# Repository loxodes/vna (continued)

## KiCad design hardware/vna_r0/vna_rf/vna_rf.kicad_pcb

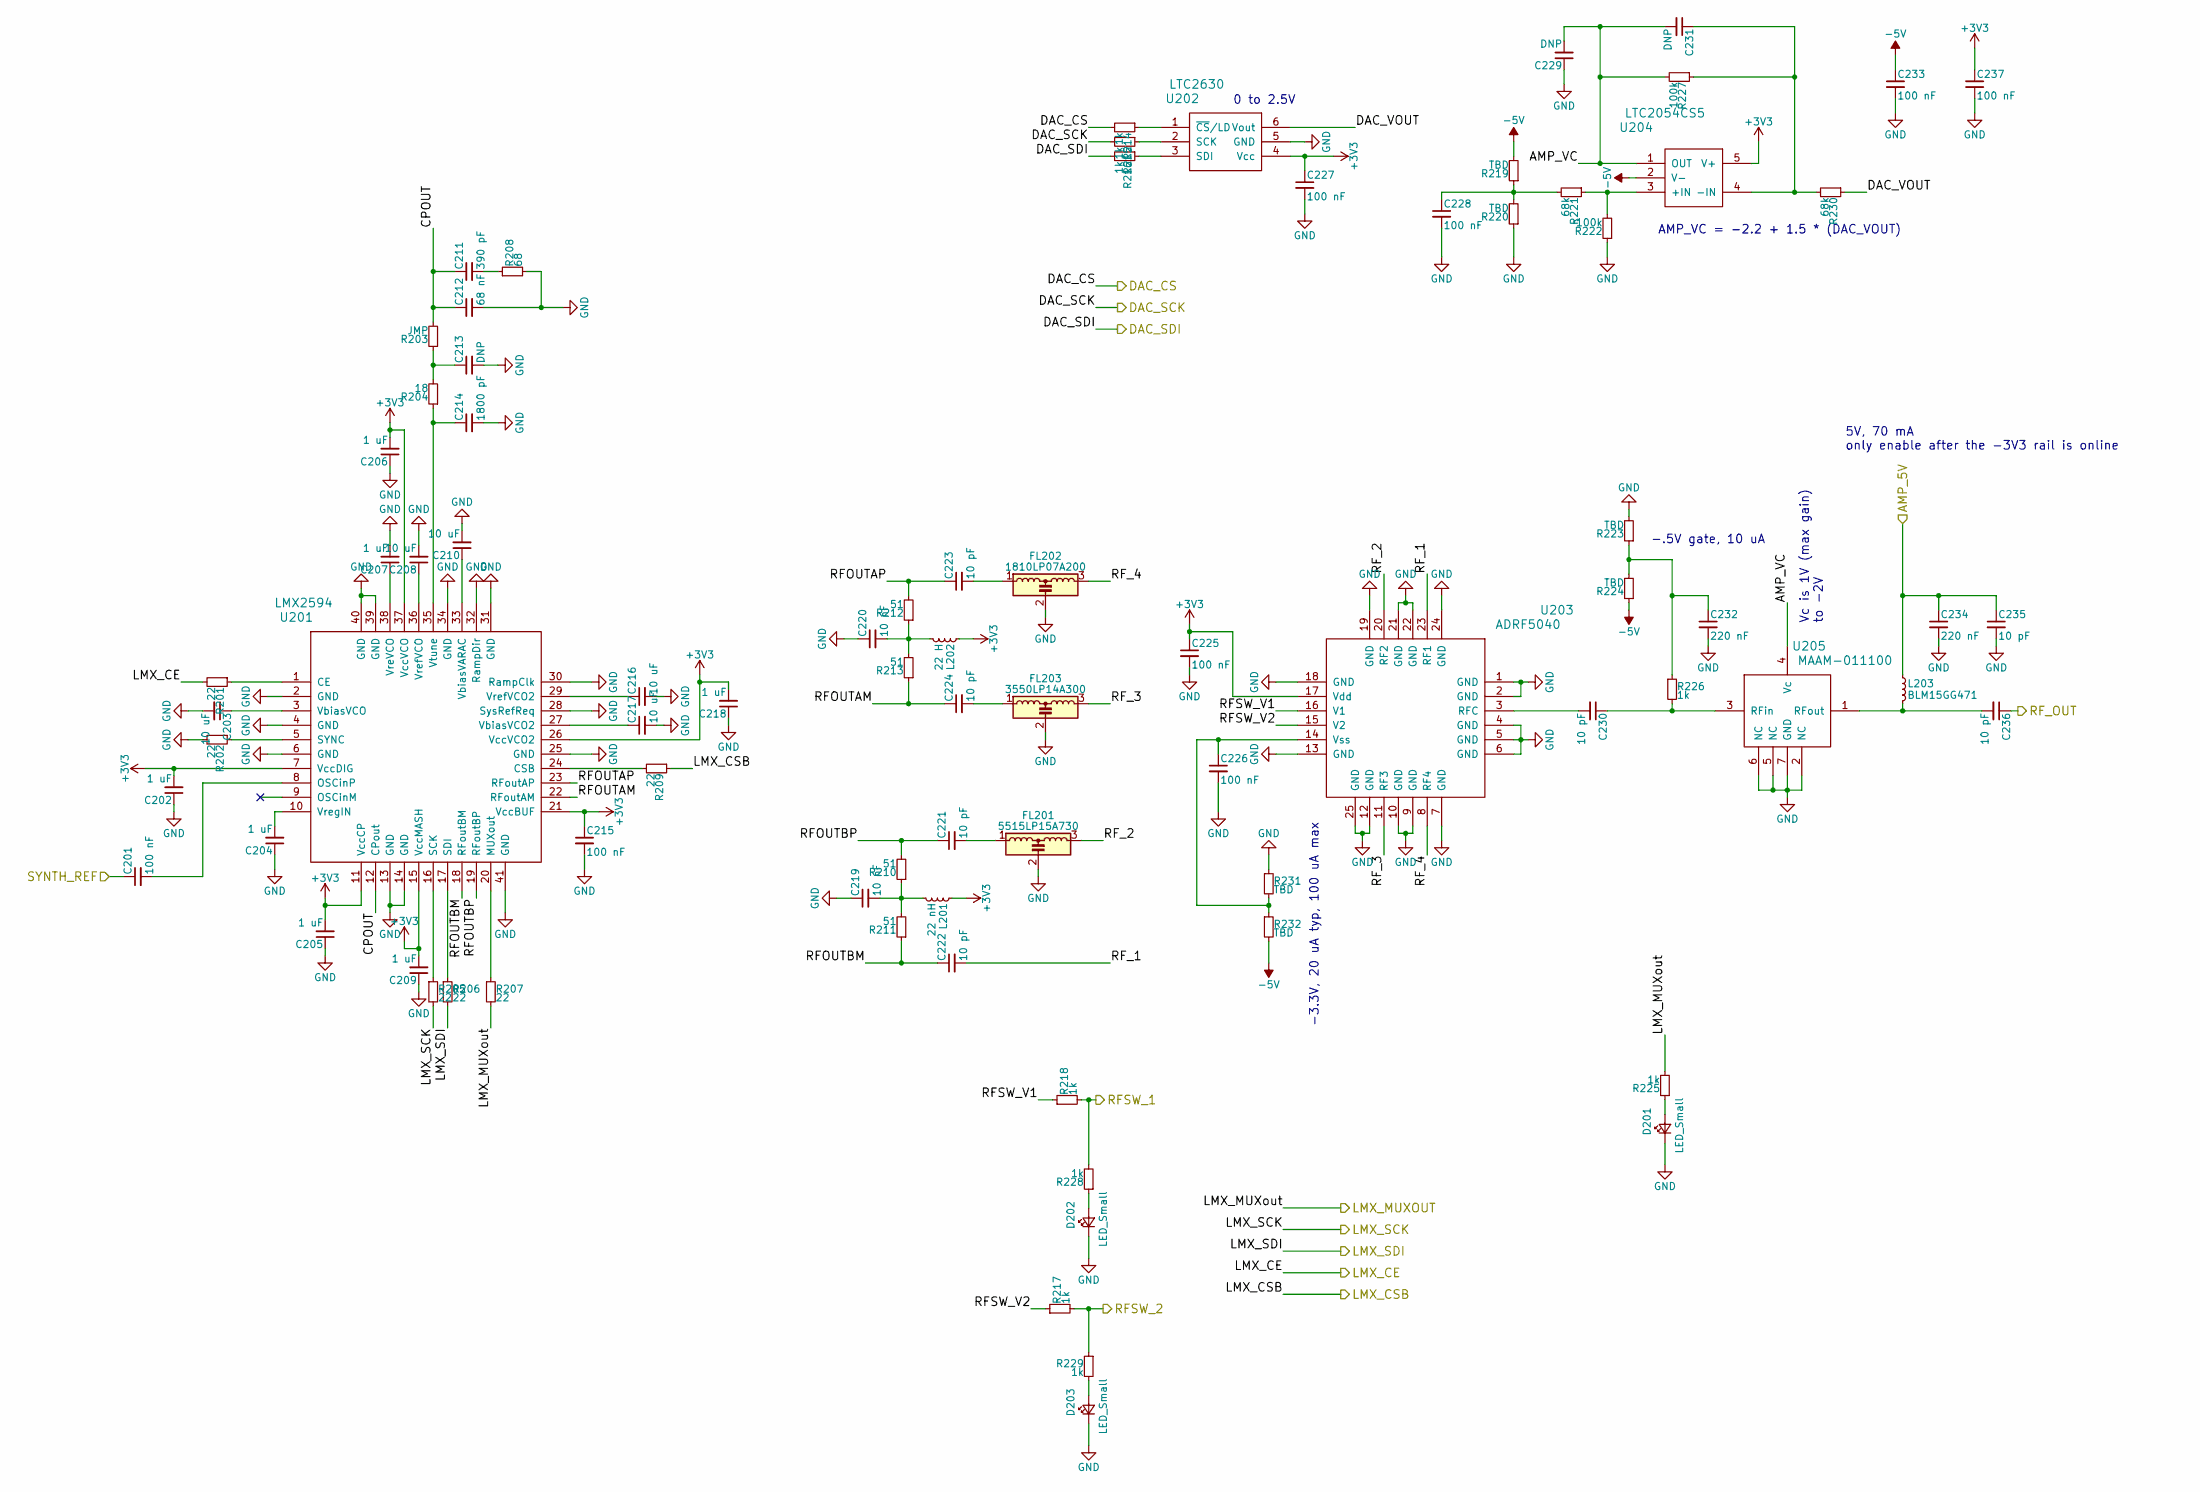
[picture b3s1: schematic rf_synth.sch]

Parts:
C201, C215, C225, C226, C227, C228, C233, C237: 100 nF; C_0402
C202, C204, C205, C206, C207, C209, C218: 1 uF; C_0402
C203, C208, C210, C216, C217: 10 uF; C_0603
C211: 390 pF; C_0402
C212: 68 nF; C_0402
C213, C229, C231: DNP; C_0402
C214: 1800 pF; C_0402
C219, C220: 10 nF; C_0402
C221, C222, C223, C224, C230, C235, C236: 10 pF; C_0402
C232, C234: 220 nF; C_0402
D201, D202, D203: LED_Small; LED_0603
FL201: 5515LP15A730
FL202: 1810LP07A200
FL203: 3550LP14A300
L201: 22 nH; R_0402
L202: 22 H; R_0402
L203: BLM15GG471; R_0402
R201, R202, R205, R206, R207, R209: 22; R_0402
R203: JMP; R_0402
R204: 18; R_0402
R208: 68; R_0402
R210, R211, R212, R213: 51; R_0402
R214, R215, R216, R217, R218, R225, R226, R228, R229: 1k; R_0402
R219, R220, R223, R224, R231, R232: TBD; R_0402
R221, R230: 68k; R_0402
R222, R227: 100k; R_0402
U201: LMX2594; QFN-40-1EP_6x6mm_Pitch0.5mm
U202: LTC2630; SC-70-6
U203: ADRF5040; QFN-24-1EP_4x4mm_Pitch0.5mm
U204: LTC2054CS5; SOT-23-5
U205: MAAM-011100; TDFN6

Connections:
+3V3: C202.2, C205.2, C206.2, C209.2, C215.1, C218.2, C225.1, C227.1, C237.1, L201.1, L202.1, U201.7 (VccDIG), U201.11 (VccCP), U201.15 (VccMASH), U201.21 (VccBUF), U201.26 (VccVCO2), U201.37 (VccVCO), U202.4 (Vcc), U203.17 (Vdd), U204.5 (V+); also elsewhere on the board
-5V: C233.1, R219.2, R224.1, R232.2, U204.2 (V-); also elsewhere on the board
/AMP_5V: C234.1, C235.1, L203.1; also elsewhere on the board
/DAC_CS: R214.2; also elsewhere on the board
/DAC_SCK: R215.2; also elsewhere on the board
/DAC_SDI: R216.2; also elsewhere on the board
/LMX_CE: R201.2; also elsewhere on the board
/LMX_CS: R209.1; also elsewhere on the board
/LMX_MUXOUT: R207.2, R225.2; also elsewhere on the board
/LMX_SCK: R205.2; also elsewhere on the board
/LMX_SDI: R206.2; also elsewhere on the board
/RFSW_1: R218.2, R228.2; also elsewhere on the board
/RFSW_2: R217.2, R229.1; also elsewhere on the board
/conn_power/SYNTH_REF: C201.1; also elsewhere on the board
/port_switch/RFIN: C236.1; also elsewhere on the board
/rf_synth/AMP_VC: C229.2, C231.2, R227.2, U204.1 (OUT), U205.4 (Vc)
/rf_synth/CPOUT: C211.1, C212.1, R203.2, U201.12 (CPout)
/rf_synth/DAC_VOUT: R230.1, U202.6 (Vout)
/rf_synth/RFOUTAM: C224.1, R213.1, U201.22 (RFoutAM)
/rf_synth/RFOUTAP: C223.1, R212.2, U201.23 (RFoutAP)
/rf_synth/RFOUTBM: C222.1, R211.1, U201.18 (RFoutBM)
/rf_synth/RFOUTBP: C221.1, R210.2, U201.19 (RFoutBP)
/rf_synth/RFSW_V1: R218.1, U203.16 (V1)
/rf_synth/RFSW_V2: R217.1, U203.15 (V2)
/rf_synth/RF_1: C222.2, U203.23 (RF1)
/rf_synth/RF_2: FL201.3, U203.20 (RF2)
/rf_synth/RF_3: FL203.3, U203.11 (RF3)
/rf_synth/RF_4: FL202.3, U203.8 (RF4)
GND: C202.1, C203.2, C204.1, C205.1, C206.1, C207.2, C208.2, C209.1, C210.2, C212.2, C213.2, C214.2, C215.2, C216.2, C217.2, C218.1, C219.1, C220.1, C225.2, C226.2, C227.2, C228.2, C229.1, C232.2, C233.2, C234.2, C235.2, C237.2, D201.1 (K), D202.1 (K), D203.1 (K), FL201.2, FL202.2, FL203.2, R202.2, R208.2, R220.1, R222.1, R223.2, R231.1, U201.2 (GND), U201.4 (GND), U201.6 (GND), U201.13 (GND), U201.14 (GND), U201.25 (GND), U201.28 (SysRefReq), U201.30 (RampClk), U201.31 (GND), U201.32 (RampDir), U201.34 (GND), U201.39 (GND), U201.40 (GND), U201.41 (GND), U202.5 (GND), U203.1 (GND), U203.2 (GND), U203.4 (GND), U203.5 (GND), U203.6 (GND), U203.7 (GND), U203.9 (GND), U203.10 (GND), U203.12 (GND), U203.13 (GND), U203.18 (GND), U203.19 (GND), U203.21 (GND), U203.22 (GND), U203.24 (GND), U203.25 (GND), U205.2 (NC), U205.5 (NC), U205.6 (NC), U205.7 (GND); also elsewhere on the board
unnamed: C201.2, U201.8 (OSCinP)
unnamed: C203.1, U201.3 (VbiasVCO)
unnamed: C204.2, U201.10 (VregIN)
unnamed: C207.1, U201.38 (VreVCO)
unnamed: C208.1, U201.36 (VrefVCO)
unnamed: C210.1, U201.33 (VbiasVARAC)
unnamed: C211.2, R208.1
unnamed: C213.1, R203.1, R204.2
unnamed: C214.1, R204.1, U201.35 (Vtune)
unnamed: C216.1, U201.29 (VrefVCO2)
unnamed: C217.1, U201.27 (VbiasVCO2)
unnamed: C219.2, L201.2, R210.1, R211.2
unnamed: C220.2, L202.2, R212.1, R213.2
unnamed: C221.2, FL201.1
unnamed: C223.2, FL202.1
unnamed: C224.2, FL203.1
unnamed: C226.1, R231.2, R232.1, U203.14 (Vss)
unnamed: C228.1, R219.1, R220.2, R221.2
unnamed: C230.1, R226.2, U205.3 (RFin)
unnamed: C230.2, U203.3 (RFC)
unnamed: C231.1, R227.1, R230.2, U204.4 (-IN)
unnamed: C232.1, R223.1, R224.2, R226.1
unnamed: C236.2, L203.2, U205.1 (RFout)
unnamed: D201.2 (A), R225.1
unnamed: D202.2 (A), R228.1
unnamed: D203.2 (A), R229.2
unnamed: R201.1, U201.1 (CE)
unnamed: R202.1, U201.5 (SYNC)
unnamed: R205.1, U201.16 (SCK)
unnamed: R206.1, U201.17 (SDI)
unnamed: R207.1, U201.20 (MUXout)
unnamed: R209.2, U201.24 (CSB)
unnamed: R214.1, U202.1 (~CS~/LD)
unnamed: R215.1, U202.2 (SCK)
unnamed: R216.1, U202.3 (SDI)
unnamed: R221.1, R222.2, U204.3 (+IN)

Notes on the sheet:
-.5V gate, 10 uA
5V, 70 mA only enable after the -3V3 rail is online
Vc is 1V (max gain) to -2V
0 to 2.5V
AMP_VC = -2.2 + 1.5 * (DAC_VOUT)
-3.3V, 20 uA typ, 100 uA max

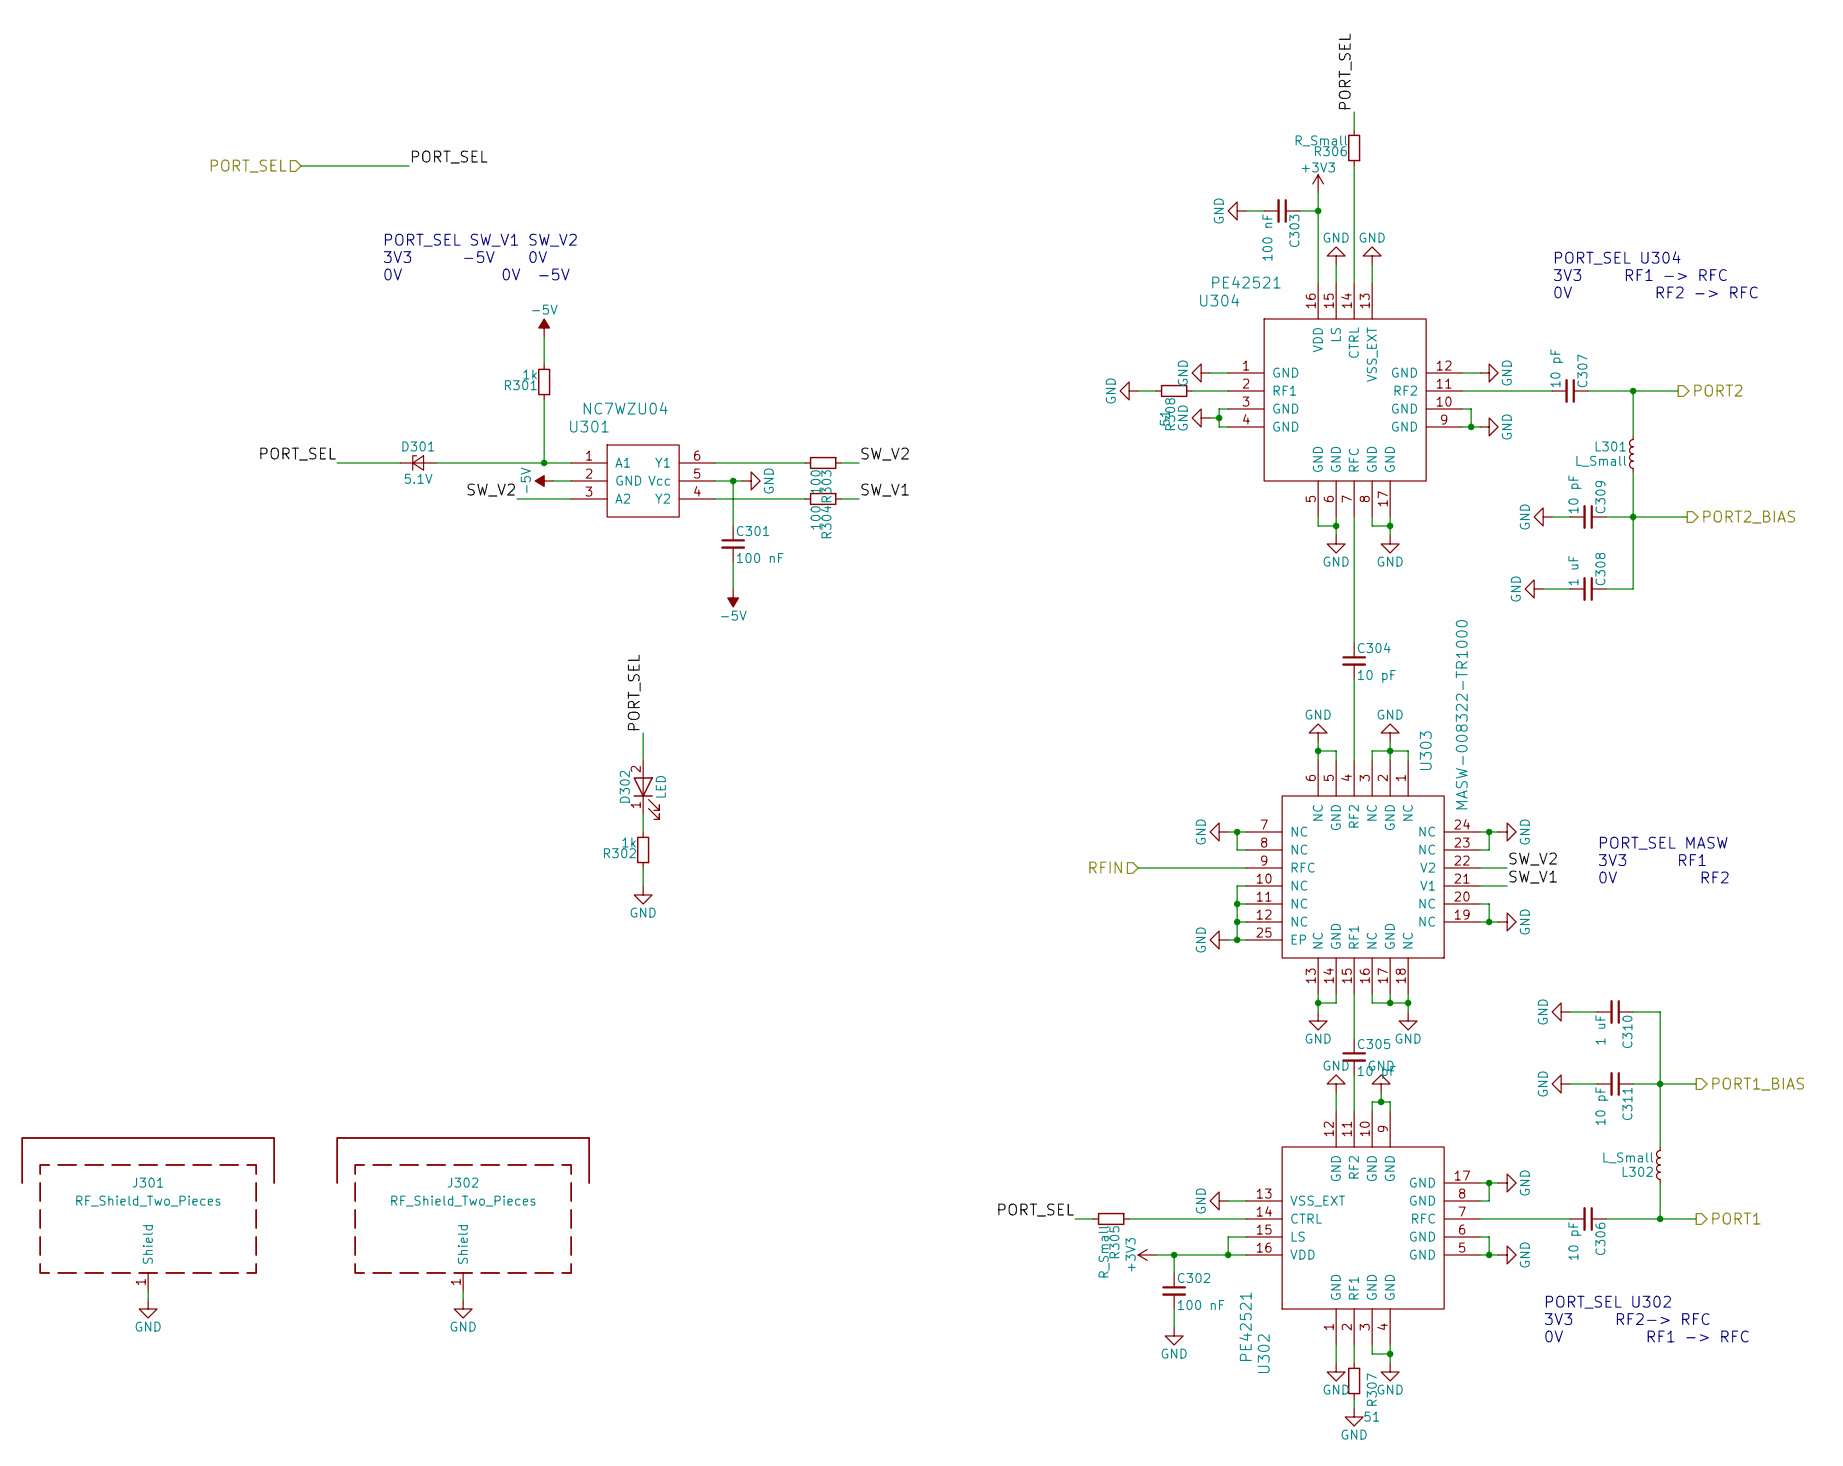
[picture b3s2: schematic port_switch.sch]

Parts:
C301, C302, C303: 100 nF; C_0402
C304, C305, C306, C307, C309, C311: 10 pF; C_0402
C308, C310: 1 uF; C_0805
D301: 5.1V; SOD-323
D302: LED; LED_0603
J301, J302: RF_Shield_Two_Pieces; Laird_Technologies_BMI-S-202-F_16.50x16.50mm
L301, L302: L_Small; ATC506WLS
R301, R302: 1k; R_0402
R303, R304: 100; R_0402
R305, R306: R_Small; R_0402
R307, R308: 51; R_0402
U301: NC7WZU04; SC-70-6
U302, U304: PE42521; QFN-16-1EP_3x3mm_Pitch0.5mm
U303: MASW-008322-TR1000; QFN-24-1EP_4x4mm_Pitch0.5mm

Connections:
+3V3: C302.1, C303.1, U302.15 (LS), U302.16 (VDD), U304.16 (VDD); also elsewhere on the board
-5V: C301.2, R301.2, U301.2 (GND); also elsewhere on the board
/PORT1_BIAS: C310.1, C311.1, L302.2; also elsewhere on the board
/PORT2_BIAS: C308.1, C309.1, L301.2; also elsewhere on the board
/conn_power/PORT1: C306.1, L302.1; also elsewhere on the board
/conn_power/PORT2: C307.1, L301.1; also elsewhere on the board
/conn_power/PORT_SEL: D301.1 (K), D302.2 (A), R305.2, R306.2; also elsewhere on the board
/port_switch/RFIN: U303.9 (RFC); also elsewhere on the board
/port_switch/SW_V1: R304.1, U303.21 (V1)
/port_switch/SW_V2: R303.1, U301.3 (A2), U303.22 (V2)
GND: C301.1, C302.2, C303.2, C308.2, C309.2, C310.2, C311.2, J301.1, J302.1, R302.1, R307.1, R308.1, U301.5 (Vcc), U302.1 (GND), U302.3 (GND), U302.4 (GND), U302.5 (GND), U302.6 (GND), U302.8 (GND), U302.9 (GND), U302.10 (GND), U302.12 (GND), U302.13 (VSS_EXT), U302.17 (GND), U303.1 (NC), U303.2 (GND), U303.3 (NC), U303.5 (GND), U303.6 (NC), U303.7 (NC), U303.8 (NC), U303.10 (NC), U303.11 (NC), U303.12 (NC), U303.13 (NC), U303.14 (GND), U303.16 (NC), U303.17 (GND), U303.18 (NC), U303.19 (NC), U303.20 (NC), U303.23 (NC), U303.24 (NC), U303.25 (EP), U304.1 (GND), U304.3 (GND), U304.4 (GND), U304.5 (GND), U304.6 (GND), U304.8 (GND), U304.9 (GND), U304.10 (GND), U304.12 (GND), U304.13 (VSS_EXT), U304.15 (LS), U304.17 (GND); also elsewhere on the board
unnamed: C304.1, U304.7 (RFC)
unnamed: C304.2, U303.4 (RF2)
unnamed: C305.1, U303.15 (RF1)
unnamed: C305.2, U302.11 (RF2)
unnamed: C306.2, U302.7 (RFC)
unnamed: C307.2, U304.11 (RF2)
unnamed: D301.2 (A), R301.1, U301.1 (A1)
unnamed: D302.1 (K), R302.2
unnamed: R303.2, U301.6 (Y1)
unnamed: R304.2, U301.4 (Y2)
unnamed: R305.1, U302.14 (CTRL)
unnamed: R306.1, U304.14 (CTRL)
unnamed: R307.2, U302.2 (RF1)
unnamed: R308.2, U304.2 (RF1)

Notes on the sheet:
PORT_SEL SW_V1 SW_V2 3V3 -5V 0V 0V 0V -5V
PORT_SEL MASW 3V3 RF1 0V RF2
PORT_SEL U304 3V3 RF1 -> RFC 0V RF2 -> RFC
PORT_SEL U302 3V3 RF2-> RFC 0V RF1 -> RFC

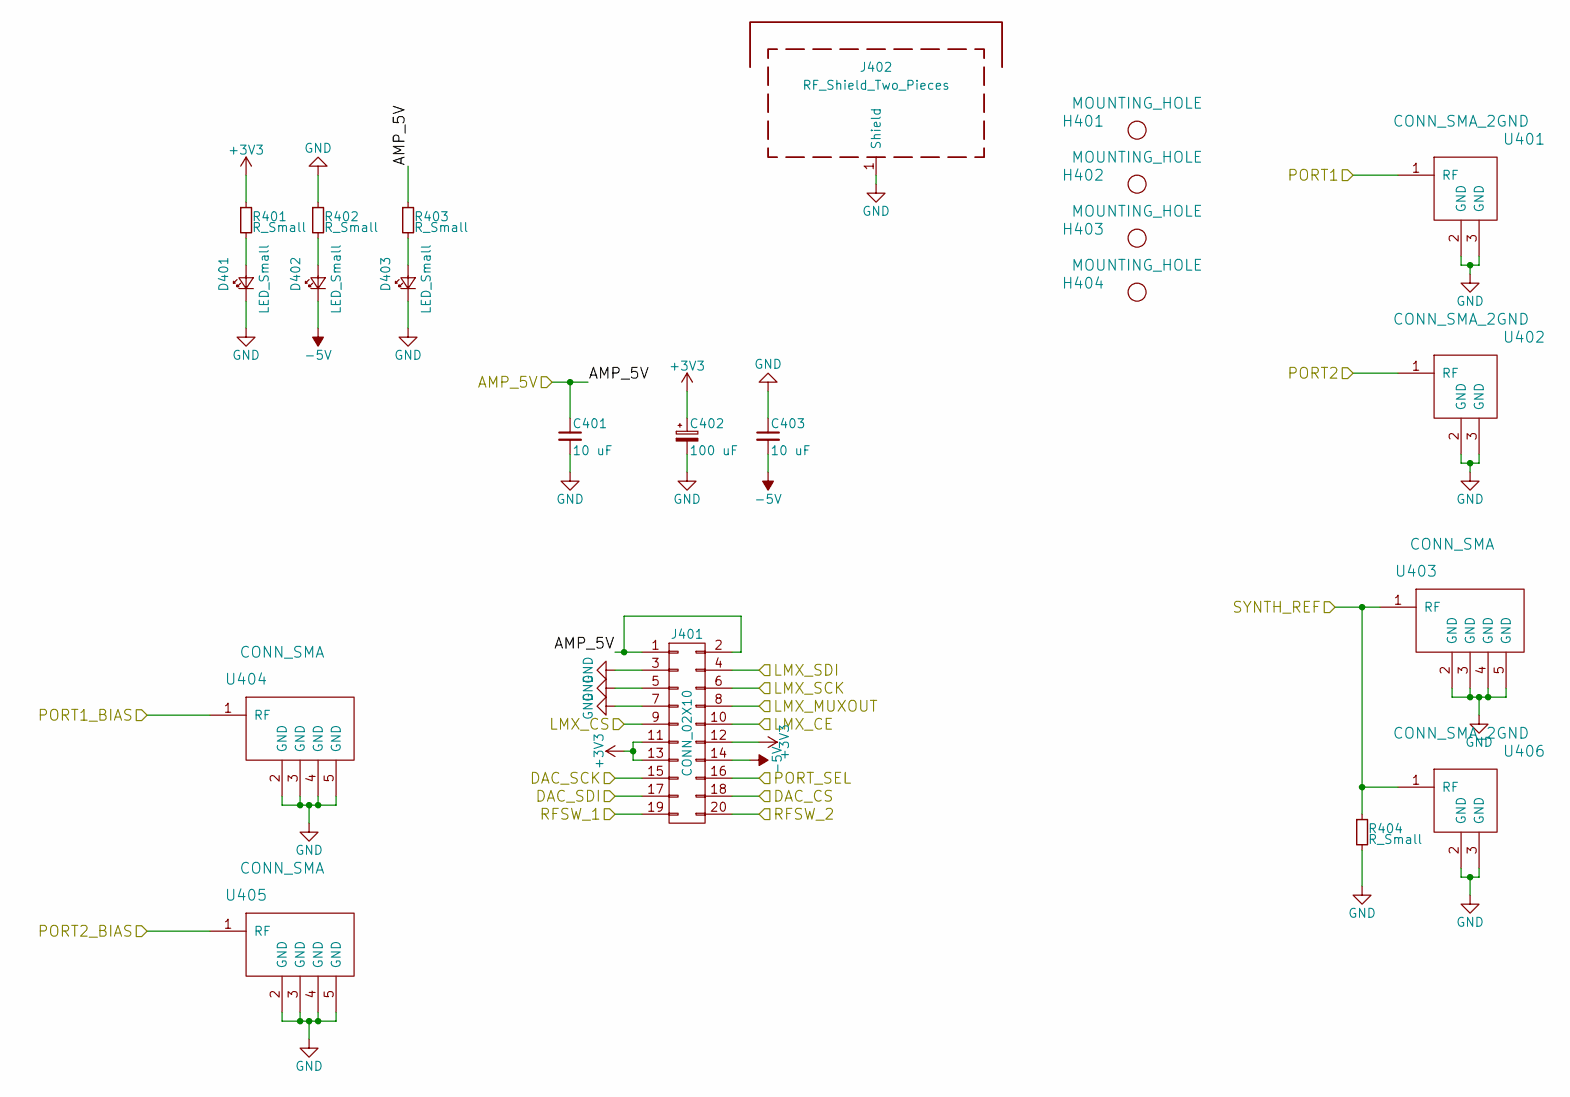
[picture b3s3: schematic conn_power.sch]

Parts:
C401, C403: 10 uF; C_0603
C402: 100 uF; c_elec_10x10
D401, D402, D403: LED_Small; LED_0603
H401, H402, H403, H404: MOUNTING_HOLE; MountingHole_2-7mm
J401: CONN_02X10; IDC_Header_Straight_20pins
J402: RF_Shield_Two_Pieces; Laird_Technologies_BMI-S-205-F_38.10x25.40mm
R401, R402, R403, R404: R_Small; R_0402
U401, U402: CONN_SMA_2GND; SMA_901-10512_30MIL_OSHFR408_CPW_LAUNCH
U403, U404, U405: CONN_SMA; 732511150_sma_thin
U406: CONN_SMA_2GND; 734120110_ufl_umc

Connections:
+3V3: C402.1, J401.11, J401.12, J401.13, R401.1; also elsewhere on the board
-5V: C403.2, D402.1 (K), J401.14; also elsewhere on the board
/AMP_5V: C401.1, J401.1, J401.2, R403.1; also elsewhere on the board
/DAC_CS: J401.18; also elsewhere on the board
/DAC_SCK: J401.15; also elsewhere on the board
/DAC_SDI: J401.17; also elsewhere on the board
/LMX_CE: J401.10; also elsewhere on the board
/LMX_CS: J401.9; also elsewhere on the board
/LMX_MUXOUT: J401.8; also elsewhere on the board
/LMX_SCK: J401.6; also elsewhere on the board
/LMX_SDI: J401.4; also elsewhere on the board
/PORT1_BIAS: U404.1 (RF); also elsewhere on the board
/PORT2_BIAS: U405.1 (RF); also elsewhere on the board
/RFSW_1: J401.19; also elsewhere on the board
/RFSW_2: J401.20; also elsewhere on the board
/conn_power/PORT1: U401.1 (RF); also elsewhere on the board
/conn_power/PORT2: U402.1 (RF); also elsewhere on the board
/conn_power/PORT_SEL: J401.16; also elsewhere on the board
/conn_power/SYNTH_REF: R404.1, U403.1 (RF), U406.1 (RF); also elsewhere on the board
GND: C401.2, C402.2, C403.1, D401.1 (K), D403.1 (K), J401.3, J401.5, J401.7, J402.1, R402.1, R404.2, U401.2 (GND), U401.3 (GND), U402.2 (GND), U402.3 (GND), U403.2 (GND), U403.3 (GND), U403.4 (GND), U403.5 (GND), U404.2 (GND), U404.3 (GND), U404.4 (GND), U404.5 (GND), U405.2 (GND), U405.3 (GND), U405.4 (GND), U405.5 (GND), U406.2 (GND), U406.3 (GND); also elsewhere on the board
unnamed: D401.2 (A), R401.2
unnamed: D402.2 (A), R402.2
unnamed: D403.2 (A), R403.2

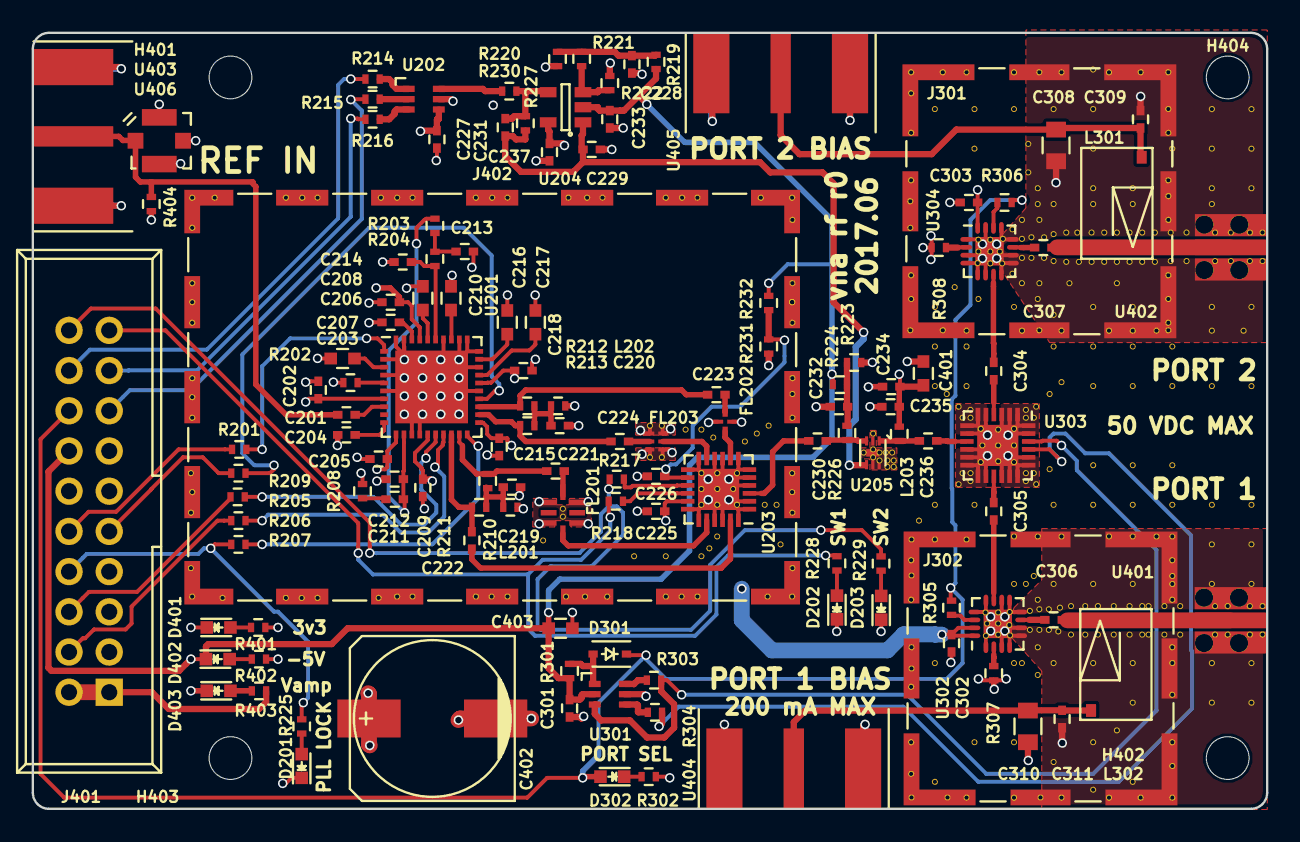
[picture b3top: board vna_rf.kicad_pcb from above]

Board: 4 copper layers, 78.0 x 49.0 mm, 134 parts (0 on the bottom side), 89 nets.

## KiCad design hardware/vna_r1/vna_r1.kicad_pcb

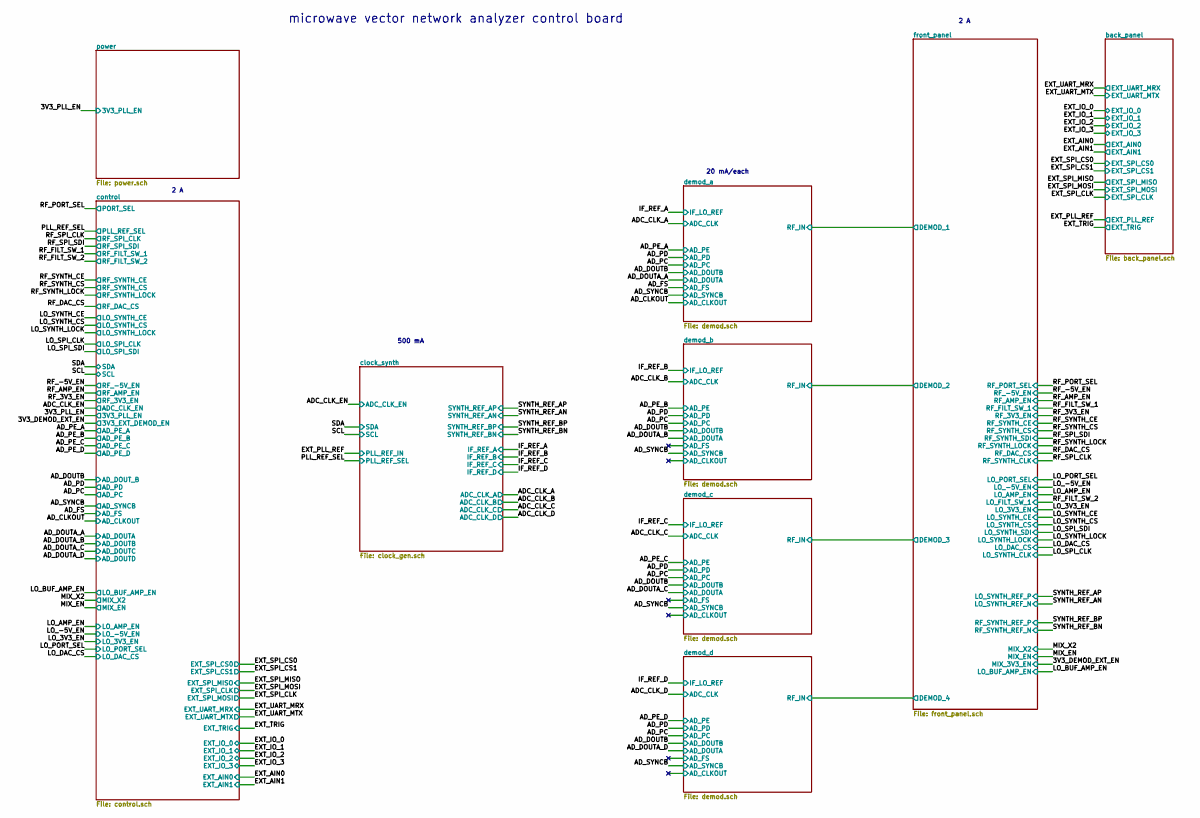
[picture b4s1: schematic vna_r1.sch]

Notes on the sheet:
microwave vector network analyzer control board
20 mA/each
2 A
500 mA
